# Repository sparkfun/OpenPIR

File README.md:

OpenPIR
==========

[![OpenPIR
Image](https://cdn.sparkfun.com/assets/parts/1/1/7/0/6/13968-01.jpg)*OpenPIR
(SEN-13968)*](https://www.sparkfun.com/products/13968)

OpenPIR is an open source general purpose passive long-wave infrared motion 
detection sensor.

Repository Contents
-------------------
* **/Documentation** - Datasheets for parts used in this design
* **/Hardware** - All Eagle design files
* **/Production** - Panel files used by SFE production for ordering

License Information
-------------------
The hardware is released under [Creative Commons Share-alike
4.0](http://creativecommons.org/licenses/by-sa/4.0/).  
All other code is open source so please feel free to do anything you want with
it; you buy me a beer if you use this and we meet someday ([Beerware
license](http://en.wikipedia.org/wiki/Beerware)).

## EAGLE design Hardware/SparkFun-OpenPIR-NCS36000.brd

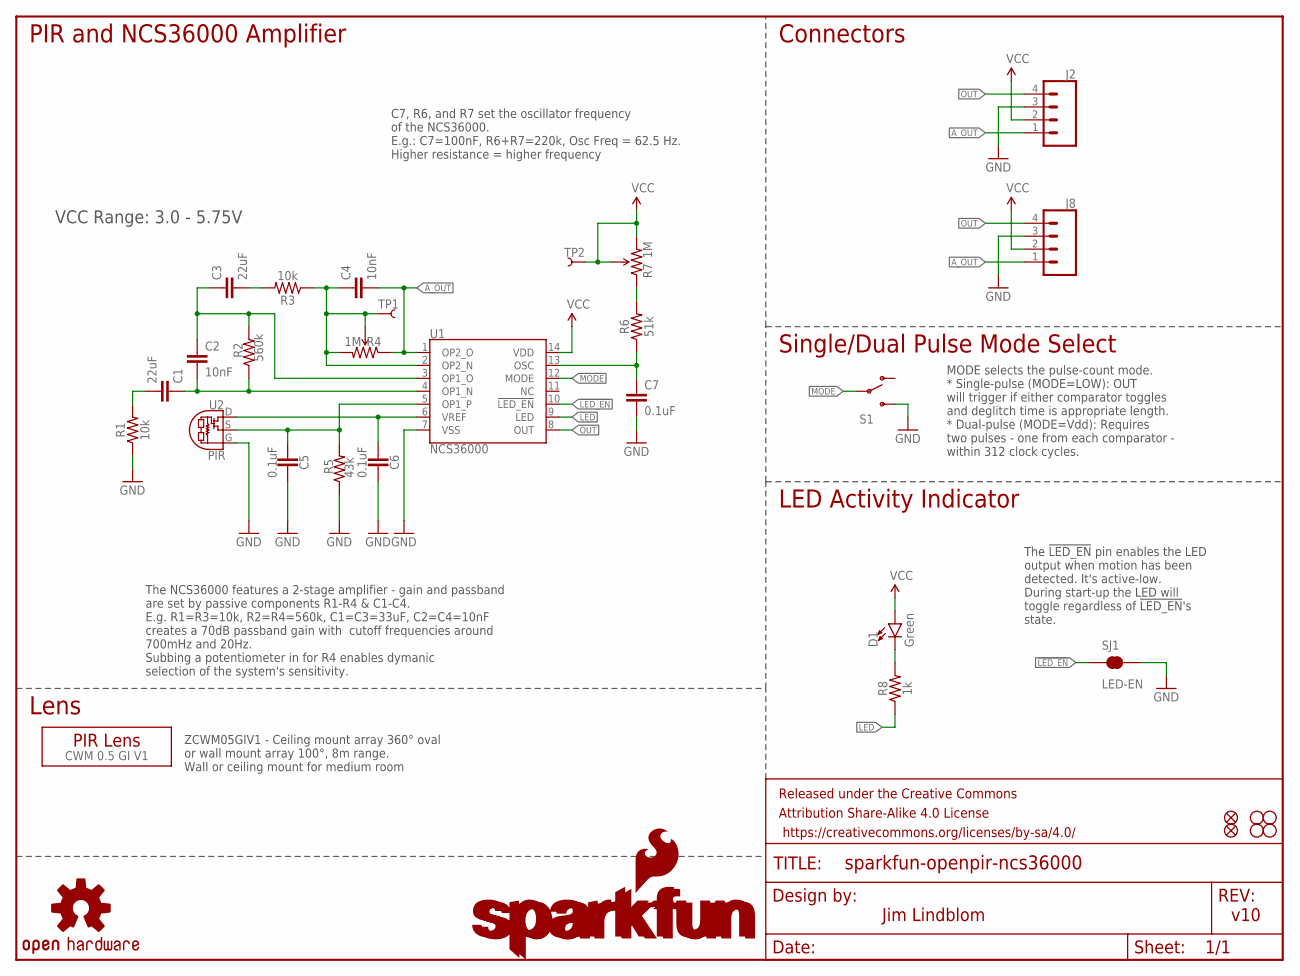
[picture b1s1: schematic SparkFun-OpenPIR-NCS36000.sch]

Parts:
C1, C3: 22uF; 0805
C2, C4: 10nF; 0603
C5, C6, C7: 0.1uF; 0603
D1: Green; LED-1206-BOTTOM
FD1, FD2: FIDUCIALUFIDUCIAL; MICRO-FIDUCIAL
FRAME1: FRAME-LETTER; CREATIVE_COMMONS
H1, H2, H3, H4: STAND-OFF
J2: CONN_04JST-PTH-VERT-NS; JST-4-PTH-VERT-NS
J8: CONN_04NO_SILK_ALL_ROUND; 1X04_NO_SILK_ALL_ROUND
LOGO1: SFE_LOGO_NAME_FLAME.1_INCH; SFE_LOGO_NAME_FLAME_.1
LOGO3: SFE_LOGO_NAME.1_INCH; SFE_LOGO_NAME_.1
LOGO4: OSHW-LOGOS; OSHW-LOGO-S
R1, R3: 10k; 0603
R2: 560k; 0603
R4, R7: 1M; TRIMPOT-TC33X
R5: 43k; 0603
R6: 51k; 0603
R8: 1k; 0603
S1: SWITCH-SPDT-SMD-A; SWITCH-SPST-SMD-A
SJ1: LED-EN; SJ_2S
TP1, TP2: TEST-POINT3X5; PAD.03X.05
U1: NCS36000; SO14
U2: PIR
U$1: CWM 0.5 GI V1; LENS-CWM-0.5-GI-V1

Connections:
!LED_EN!: SJ1.1, U1.10 (!LED_EN!)
A_OUT: C4.2, J2.1, J8.1, R4.1 (CCW), U1.1 (OP2_O)
GND: C5.2, C6.2, C7.2, J2.3, J8.3, R1.1, R5.1, S1.3 (S), SJ1.2, U1.7 (VSS), U2.G
LED: R8.1, U1.9 (LED)
MODE: S1.2, U1.12 (MODE)
unnamed: C5.1, R5.2, U1.5 (OP1_P), U2.S
unnamed: C6.1, U1.6 (VREF), U2.D
unnamed: C1.2, R1.2
unnamed: C3.2, R3.2
unnamed: C1.1, C2.2, R2.1, U1.4 (OP1_N)
unnamed: C2.1, C3.1, R2.2, U1.3 (OP1_O)
unnamed: C4.1, R3.1, R4.2 (WIPER), R4.3 (CW), TP1.P$1, U1.2 (OP2_N)
unnamed: C7.1, R6.1, U1.13 (OSC)
unnamed: D1.C, R8.2
unnamed: R6.2, R7.1 (CCW)
OUT: J2.4, J8.4, U1.8 (OUT)
VCC: D1.A, J2.2, J8.2, R7.2 (WIPER), R7.3 (CW), TP2.P$1, U1.14 (VDD)

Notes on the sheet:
The !LED_EN! pin enables the LED output when motion has been detected. It's active-low. During start-up the LED will toggle regardless of !LED_EN!'s state.
MODE selects the pulse-count mode. * Single-pulse (MODE=LOW): OUT will trigger if either comparator toggles and deglitch time is appropriate length. * Dual-pulse (MODE=Vdd): Requires two pulses - one from each comparator - within 312 clock cycles.
Jim Lindblom
v10
VCC Range: 3.0 - 5.75V
The NCS36000 features a 2-stage amplifier - gain and passband are set by passive components R1-R4 & C1-C4. E.g. R1=R3=10k, R2=R4=560k, C1=C3=33uF, C2=C4=10nF creates a 70dB passband gain with cutoff frequencies around 700mHz and 20Hz. Subbing a potentiometer in for R4 enables dymanic selection of t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
C7, R6, and R7 set the oscillator frequency of the NCS36000. E.g.: C7=100nF, R6+R7=220k, Osc Freq = 62.5 Hz. Higher resistance = higher frequency
ZCWM05GIV1 - Ceiling mount array 360° oval or wall mount array 100°, 8m range. Wall or ceiling mount for medium room
PIR and NCS36000 Amplifier
Connectors
Single/Dual Pulse Mode Select
LED Activity Indicator
Lens

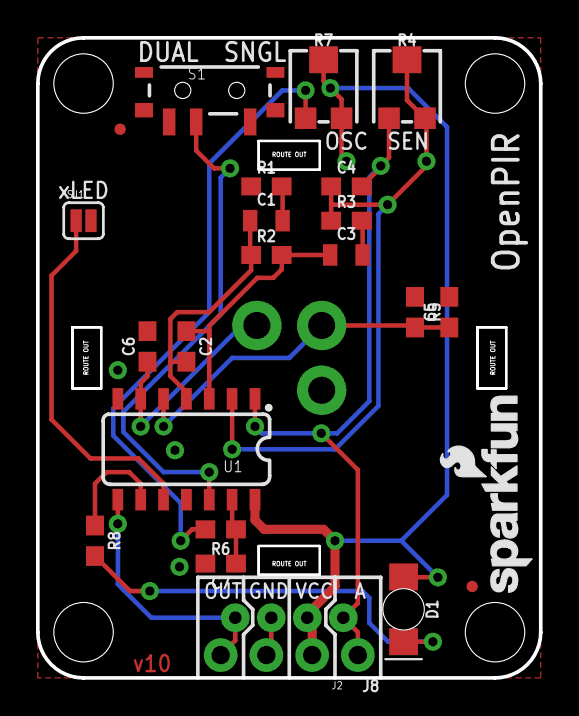
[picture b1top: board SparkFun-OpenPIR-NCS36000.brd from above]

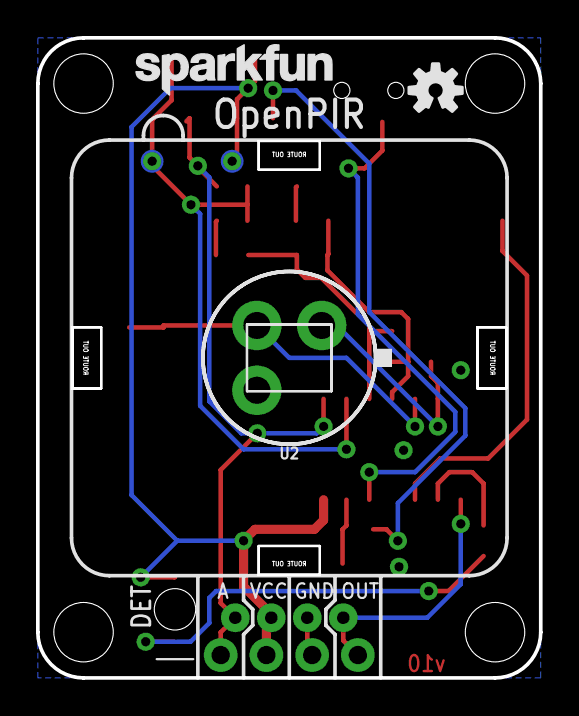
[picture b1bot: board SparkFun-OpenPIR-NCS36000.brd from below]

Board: 2 copper layers, 27.9 x 35.6 mm, 35 parts (6 on the bottom side), 17 nets.

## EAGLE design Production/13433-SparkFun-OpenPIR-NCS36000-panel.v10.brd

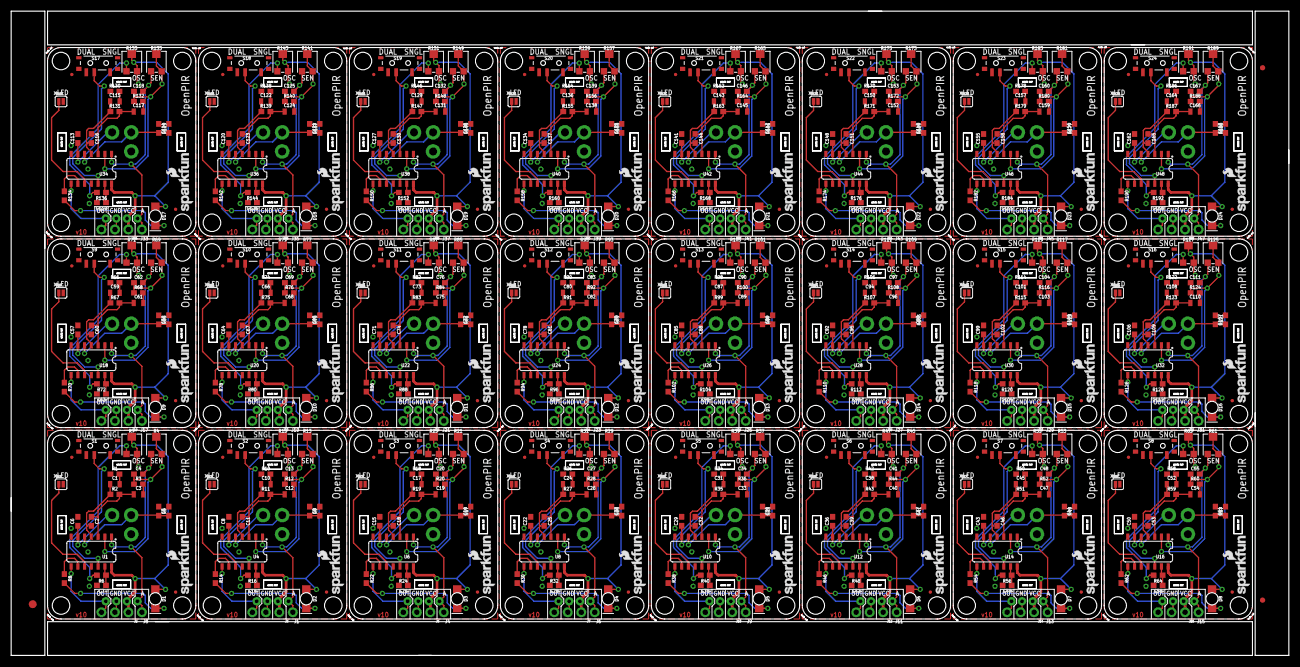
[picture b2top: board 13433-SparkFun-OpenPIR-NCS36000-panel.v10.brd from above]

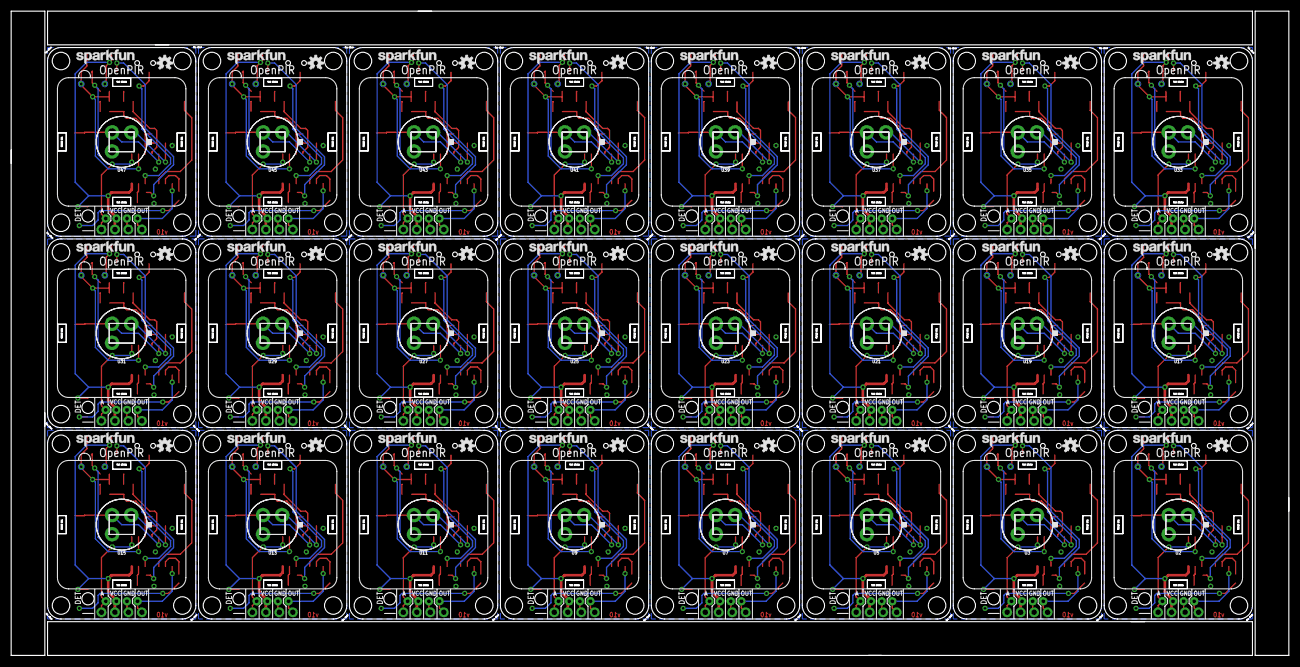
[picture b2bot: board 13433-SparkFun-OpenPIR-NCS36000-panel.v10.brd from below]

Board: 2 copper layers, 240.8 x 121.4 mm, 819 parts (144 on the bottom side), 408 nets.

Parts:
C1, C3, C10, C12, C17, C19, C24, C26, C31, C33, C38, C40, C45, C47, C52, C54, C59, C61, C66, C68, C73, C75, C80, C82, C87, C89, C94, C96, C101, C103, C108, C110, C115, C117, C122, C124, C129, C131, C136, C138, C143, C145, C150, C152, C157, C159, C164, C166: 22uF; 0805
C2, C4, C11, C13, C18, C20, C25, C27, C32, C34, C39, C41, C46, C48, C53, C55, C60, C62, C67, C69, C74, C76, C81, C83, C88, C90, C95, C97, C102, C104, C109, C111, C116, C118, C123, C125, C130, C132, C137, C139, C144, C146, C151, C153, C158, C160, C165, C167: 10nF; 0603
C5, C6, C7, C8, C9, C14, C15, C16, C21, C22, C23, C28, C29, C30, C35, C36, C37, C42, C43, C44, C49, C50, C51, C56, C57, C58, C63, C64, C65, C70, C71, C72, C77, C78, C79, C84, C85, C86, C91, C92, C93, C98, C99, C100, C105, C106, C107, C112, C113, C114, C119, C120, C121, C126, C127, C128, C133, C134, C135, C140, C141, C142, C147, C148, C149, C154, C155, C156, C161, C162, C163, C168: 0.1uF; 0603
D1, D2, D3, D4, D5, D6, D7, D8, D9, D10, D11, D12, D13, D14, D15, D16, D17, D18, D19, D20, D21, D22, D23, D24: Green; LED-1206-BOTTOM
E$1: FIDUCIAL-1.5X3
E$5, E$6: FIDUCIAL-1X2
FD1, FD2, FD3, FD4, FD5, FD6, FD7, FD8, FD9, FD10, FD11, FD12, FD13, FD14, FD15, FD16, FD17, FD18, FD19, FD20, FD21, FD22, FD23, FD24, FD25, FD26, FD27, FD28, FD29, FD30, FD31, FD32, FD33, FD34, FD35, FD36, FD37, FD38, FD39, FD40, FD41, FD42, FD43, FD44, FD45, FD46, FD47, FD48: FIDUCIALUFIDUCIAL; MICRO-FIDUCIAL
H1, H2, H3, H4, H5, H6, H7, H8, H9, H10, H11, H12, H13, H14, H15, H16, H17, H18, H19, H20, H21, H22, H23, H24, H25, H26, H27, H28, H29, H30, H31, H32, H33, H34, H35, H36, H37, H38, H39, H40, H41, H42, H43, H44, H45, H46, H47, H48, H49, H50, H51, H52, H53, H54, H55, H56, H57, H58, H59, H60, H61, H62, H63, H64, H65, H66, H67, H68, H69, H70, H71, H72, H73, H74, H75, H76, H77, H78, H79, H80, H81, H82, H83, H84, H85, H86, H87, H88, H89, H90, H91, H92, H93, H94, H95, H96: STAND-OFF
J1, J4, J6, J8, J9, J11, J13, J15, J17, J19, J21, J23, J25, J27, J29, J31, J33, J35, J37, J39, J41, J43, J45, J47: 1X04_NO_SILK_ALL_ROUND
J2, J3, J5, J7, J10, J12, J14, J16, J18, J20, J22, J24, J26, J28, J30, J32, J34, J36, J38, J40, J42, J44, J46, J48: JST-4-PTH-VERT-NS
LOGO1, LOGO2, LOGO7, LOGO10, LOGO13, LOGO16, LOGO19, LOGO22, LOGO25, LOGO28, LOGO31, LOGO34, LOGO37, LOGO40, LOGO43, LOGO46, LOGO49, LOGO52, LOGO55, LOGO58, LOGO61, LOGO64, LOGO67, LOGO70: SFE_LOGO_NAME_FLAME.1_INCH; SFE_LOGO_NAME_FLAME_.1
LOGO3, LOGO5, LOGO8, LOGO11, LOGO14, LOGO17, LOGO20, LOGO23, LOGO26, LOGO29, LOGO32, LOGO35, LOGO38, LOGO41, LOGO44, LOGO47, LOGO50, LOGO53, LOGO56, LOGO59, LOGO62, LOGO65, LOGO68, LOGO71: SFE_LOGO_NAME.1_INCH; SFE_LOGO_NAME_.1
LOGO4, LOGO6, LOGO9, LOGO12, LOGO15, LOGO18, LOGO21, LOGO24, LOGO27, LOGO30, LOGO33, LOGO36, LOGO39, LOGO42, LOGO45, LOGO48, LOGO51, LOGO54, LOGO57, LOGO60, LOGO63, LOGO66, LOGO69, LOGO72: OSHW-LOGOS; OSHW-LOGO-S
R1, R3, R10, R12, R18, R20, R26, R28, R34, R36, R42, R44, R50, R52, R58, R60, R66, R68, R74, R76, R82, R84, R90, R92, R98, R100, R106, R108, R114, R116, R122, R124, R130, R132, R138, R140, R146, R148, R154, R156, R162, R164, R170, R172, R178, R180, R186, R188: 10k; 0603
R2, R11, R19, R27, R35, R43, R51, R59, R67, R75, R83, R91, R99, R107, R115, R123, R131, R139, R147, R155, R163, R171, R179, R187: 560k; 0603
R4, R7, R13, R15, R21, R23, R29, R31, R37, R39, R45, R47, R53, R55, R61, R63, R69, R71, R77, R79, R85, R87, R93, R95, R101, R103, R109, R111, R117, R119, R125, R127, R133, R135, R141, R143, R149, R151, R157, R159, R165, R167, R173, R175, R181, R183, R189, R191: 1M; TRIMPOT-TC33X
R5, R9, R17, R25, R33, R41, R49, R57, R65, R73, R81, R89, R97, R105, R113, R121, R129, R137, R145, R153, R161, R169, R177, R185: 43k; 0603
R6, R16, R24, R32, R40, R48, R56, R64, R72, R80, R88, R96, R104, R112, R120, R128, R136, R144, R152, R160, R168, R176, R184, R192: 51k; 0603
R8, R14, R22, R30, R38, R46, R54, R62, R70, R78, R86, R94, R102, R110, R118, R126, R134, R142, R150, R158, R166, R174, R182, R190: 1k; 0603
S1, S2, S3, S4, S5, S6, S7, S8, S9, S10, S11, S12, S13, S14, S15, S16, S17, S18, S19, S20, S21, S22, S23, S24: SWITCH-SPST-SMD-A
SJ1, SJ2, SJ3, SJ4, SJ5, SJ6, SJ7, SJ8, SJ9, SJ10, SJ11, SJ12, SJ13, SJ14, SJ15, SJ16, SJ17, SJ18, SJ19, SJ20, SJ21, SJ22, SJ23, SJ24: LED-EN; SJ_2S
TP1, TP2, TP3, TP4, TP5, TP6, TP7, TP8, TP9, TP10, TP11, TP12, TP13, TP14, TP15, TP16, TP17, TP18, TP19, TP20, TP21, TP22, TP23, TP24, TP25, TP26, TP27, TP28, TP29, TP30, TP31, TP32, TP33, TP34, TP35, TP36, TP37, TP38, TP39, TP40, TP41, TP42, TP43, TP44, TP45, TP46, TP47, TP48: PAD.03X.05
U1, U4, U6, U8, U10, U12, U14, U16, U18, U20, U22, U24, U26, U28, U30, U32, U34, U36, U38, U40, U42, U44, U46, U48: NCS36000; SO14
U2, U3, U5, U7, U9, U11, U13, U15, U17, U19, U21, U23, U25, U27, U29, U31, U33, U35, U37, U39, U41, U43, U45, U47: PIR
U$1, U$2, U$3, U$4, U$5, U$6, U$7, U$8, U$9, U$10, U$11, U$12, U$13, U$14, U$15, U$16, U$17, U$18, U$19, U$20, U$21, U$22, U$23, U$24: CWM 0.5 GI V1; LENS-CWM-0.5-GI-V1

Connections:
!LED_EN!: SJ1.1, U1.10
!LED_EN!1: SJ2.1, U4.10
!LED_EN!2: SJ3.1, U6.10
!LED_EN!3: SJ4.1, U8.10
!LED_EN!4: SJ5.1, U10.10
!LED_EN!5: SJ6.1, U12.10
!LED_EN!6: SJ7.1, U14.10
!LED_EN!7: SJ8.1, U16.10
!LED_EN!8: SJ9.1, U18.10
!LED_EN!9: SJ10.1, U20.10
!LED_EN!10: SJ11.1, U22.10
!LED_EN!11: SJ12.1, U24.10
!LED_EN!12: SJ13.1, U26.10
!LED_EN!13: SJ14.1, U28.10
!LED_EN!14: SJ15.1, U30.10
!LED_EN!15: SJ16.1, U32.10
!LED_EN!16: SJ17.1, U34.10
!LED_EN!17: SJ18.1, U36.10
!LED_EN!18: SJ19.1, U38.10
!LED_EN!19: SJ20.1, U40.10
!LED_EN!20: SJ21.1, U42.10
!LED_EN!21: SJ22.1, U44.10
!LED_EN!22: SJ23.1, U46.10
!LED_EN!23: SJ24.1, U48.10
A_OUT: C4.2, J2.1, J8.1, R4.1, U1.1
A_OUT1: C13.2, J1.1, J3.1, R13.1, U4.1
A_OUT2: C20.2, J4.1, J5.1, R21.1, U6.1
A_OUT3: C27.2, J6.1, J7.1, R29.1, U8.1
A_OUT4: C34.2, J9.1, J10.1, R37.1, U10.1
A_OUT5: C41.2, J11.1, J12.1, R45.1, U12.1
A_OUT6: C48.2, J13.1, J14.1, R53.1, U14.1
A_OUT7: C55.2, J15.1, J16.1, R61.1, U16.1
A_OUT8: C62.2, J17.1, J18.1, R69.1, U18.1
A_OUT9: C69.2, J19.1, J20.1, R77.1, U20.1
A_OUT10: C76.2, J21.1, J22.1, R85.1, U22.1
A_OUT11: C83.2, J23.1, J24.1, R93.1, U24.1
A_OUT12: C90.2, J25.1, J26.1, R101.1, U26.1
A_OUT13: C97.2, J27.1, J28.1, R109.1, U28.1
A_OUT14: C104.2, J29.1, J30.1, R117.1, U30.1
A_OUT15: C111.2, J31.1, J32.1, R125.1, U32.1
A_OUT16: C118.2, J33.1, J34.1, R133.1, U34.1
A_OUT17: C125.2, J35.1, J36.1, R141.1, U36.1
A_OUT18: C132.2, J37.1, J38.1, R149.1, U38.1
A_OUT19: C139.2, J39.1, J40.1, R157.1, U40.1
A_OUT20: C146.2, J41.1, J42.1, R165.1, U42.1
A_OUT21: C153.2, J43.1, J44.1, R173.1, U44.1
A_OUT22: C160.2, J45.1, J46.1, R181.1, U46.1
A_OUT23: C167.2, J47.1, J48.1, R189.1, U48.1
GND: C5.2, C6.2, C7.2, J2.3, J8.3, R1.1, R5.1, S1.3, SJ1.2, U1.7, U2.G
GND1: C8.2, C9.2, C14.2, J1.3, J3.3, R9.1, R10.1, S2.3, SJ2.2, U3.G, U4.7
GND2: C15.2, C16.2, C21.2, J4.3, J5.3, R17.1, R18.1, S3.3, SJ3.2, U5.G, U6.7
GND3: C22.2, C23.2, C28.2, J6.3, J7.3, R25.1, R26.1, S4.3, SJ4.2, U7.G, U8.7
GND4: C29.2, C30.2, C35.2, J9.3, J10.3, R33.1, R34.1, S5.3, SJ5.2, U9.G, U10.7
GND5: C36.2, C37.2, C42.2, J11.3, J12.3, R41.1, R42.1, S6.3, SJ6.2, U11.G, U12.7
GND6: C43.2, C44.2, C49.2, J13.3, J14.3, R49.1, R50.1, S7.3, SJ7.2, U13.G, U14.7
GND7: C50.2, C51.2, C56.2, J15.3, J16.3, R57.1, R58.1, S8.3, SJ8.2, U15.G, U16.7
GND8: C57.2, C58.2, C63.2, J17.3, J18.3, R65.1, R66.1, S9.3, SJ9.2, U17.G, U18.7
GND9: C64.2, C65.2, C70.2, J19.3, J20.3, R73.1, R74.1, S10.3, SJ10.2, U19.G, U20.7
GND10: C71.2, C72.2, C77.2, J21.3, J22.3, R81.1, R82.1, S11.3, SJ11.2, U21.G, U22.7
GND11: C78.2, C79.2, C84.2, J23.3, J24.3, R89.1, R90.1, S12.3, SJ12.2, U23.G, U24.7
GND12: C85.2, C86.2, C91.2, J25.3, J26.3, R97.1, R98.1, S13.3, SJ13.2, U25.G, U26.7
GND13: C92.2, C93.2, C98.2, J27.3, J28.3, R105.1, R106.1, S14.3, SJ14.2, U27.G, U28.7
GND14: C99.2, C100.2, C105.2, J29.3, J30.3, R113.1, R114.1, S15.3, SJ15.2, U29.G, U30.7
GND15: C106.2, C107.2, C112.2, J31.3, J32.3, R121.1, R122.1, S16.3, SJ16.2, U31.G, U32.7
GND16: C113.2, C114.2, C119.2, J33.3, J34.3, R129.1, R130.1, S17.3, SJ17.2, U33.G, U34.7
GND17: C120.2, C121.2, C126.2, J35.3, J36.3, R137.1, R138.1, S18.3, SJ18.2, U35.G, U36.7
GND18: C127.2, C128.2, C133.2, J37.3, J38.3, R145.1, R146.1, S19.3, SJ19.2, U37.G, U38.7
GND19: C134.2, C135.2, C140.2, J39.3, J40.3, R153.1, R154.1, S20.3, SJ20.2, U39.G, U40.7
GND20: C141.2, C142.2, C147.2, J41.3, J42.3, R161.1, R162.1, S21.3, SJ21.2, U41.G, U42.7
GND21: C148.2, C149.2, C154.2, J43.3, J44.3, R169.1, R170.1, S22.3, SJ22.2, U43.G, U44.7
GND22: C155.2, C156.2, C161.2, J45.3, J46.3, R177.1, R178.1, S23.3, SJ23.2, U45.G, U46.7
GND23: C162.2, C163.2, C168.2, J47.3, J48.3, R185.1, R186.1, S24.3, SJ24.2, U47.G, U48.7
LED: R8.1, U1.9
LED1: R14.1, U4.9
LED2: R22.1, U6.9
LED3: R30.1, U8.9
LED4: R38.1, U10.9
LED5: R46.1, U12.9
LED6: R54.1, U14.9
LED7: R62.1, U16.9
LED8: R70.1, U18.9
LED9: R78.1, U20.9
LED10: R86.1, U22.9
LED11: R94.1, U24.9
LED12: R102.1, U26.9
LED13: R110.1, U28.9
LED14: R118.1, U30.9
LED15: R126.1, U32.9
LED16: R134.1, U34.9
LED17: R142.1, U36.9
LED18: R150.1, U38.9
LED19: R158.1, U40.9
LED20: R166.1, U42.9
LED21: R174.1, U44.9
LED22: R182.1, U46.9
LED23: R190.1, U48.9
MODE: S1.2, U1.12
MODE1: S2.2, U4.12
MODE2: S3.2, U6.12
MODE3: S4.2, U8.12
MODE4: S5.2, U10.12
MODE5: S6.2, U12.12
MODE6: S7.2, U14.12
MODE7: S8.2, U16.12
MODE8: S9.2, U18.12
MODE9: S10.2, U20.12
MODE10: S11.2, U22.12
MODE11: S12.2, U24.12
MODE12: S13.2, U26.12
MODE13: S14.2, U28.12
MODE14: S15.2, U30.12
MODE15: S16.2, U32.12
MODE16: S17.2, U34.12
MODE17: S18.2, U36.12
MODE18: S19.2, U38.12
MODE19: S20.2, U40.12
MODE20: S21.2, U42.12
MODE21: S22.2, U44.12
MODE22: S23.2, U46.12
MODE23: S24.2, U48.12
unnamed: C5.1, R5.2, U1.5, U2.S
unnamed: C6.1, U1.6, U2.D
unnamed: C1.2, R1.2
unnamed: C3.2, R3.2
unnamed: C1.1, C2.2, R2.1, U1.4
unnamed: C2.1, C3.1, R2.2, U1.3
unnamed: C4.1, R3.1, R4.2, R4.3, TP1.P$1, U1.2
unnamed: C7.1, R6.1, U1.13
unnamed: D1.C, R8.2
unnamed: C8.1, U3.D, U4.6
unnamed: R6.2, R7.1
unnamed: C9.1, R9.2, U3.S, U4.5
unnamed: C10.2, R10.2
unnamed: C12.2, R12.2
unnamed: C10.1, C11.2, R11.1, U4.4
unnamed: C11.1, C12.1, R11.2, U4.3
unnamed: C13.1, R12.1, R13.2, R13.3, TP3.P$1, U4.2
unnamed: C14.1, R16.1, U4.13
unnamed: D2.C, R14.2
unnamed: R15.1, R16.2
unnamed: C15.1, U5.D, U6.6
unnamed: C16.1, R17.2, U5.S, U6.5
unnamed: C17.2, R18.2
unnamed: C19.2, R20.2
unnamed: C17.1, C18.2, R19.1, U6.4
unnamed: C18.1, C19.1, R19.2, U6.3
unnamed: C20.1, R20.1, R21.2, R21.3, TP5.P$1, U6.2
unnamed: C21.1, R24.1, U6.13
unnamed: D3.C, R22.2
unnamed: R23.1, R24.2
unnamed: C22.1, U7.D, U8.6
unnamed: C23.1, R25.2, U7.S, U8.5
unnamed: C24.2, R26.2
unnamed: C26.2, R28.2
unnamed: C24.1, C25.2, R27.1, U8.4
unnamed: C25.1, C26.1, R27.2, U8.3
unnamed: C27.1, R28.1, R29.2, R29.3, TP7.P$1, U8.2
unnamed: C28.1, R32.1, U8.13
unnamed: D4.C, R30.2
unnamed: R31.1, R32.2
unnamed: C29.1, U9.D, U10.6
unnamed: C30.1, R33.2, U9.S, U10.5
unnamed: C31.2, R34.2
unnamed: C33.2, R36.2
unnamed: C31.1, C32.2, R35.1, U10.4
unnamed: C32.1, C33.1, R35.2, U10.3
unnamed: C34.1, R36.1, R37.2, R37.3, TP9.P$1, U10.2
unnamed: C35.1, R40.1, U10.13
unnamed: D5.C, R38.2
unnamed: R39.1, R40.2
unnamed: C36.1, U11.D, U12.6
unnamed: C37.1, R41.2, U11.S, U12.5
unnamed: C38.2, R42.2
unnamed: C40.2, R44.2
unnamed: C38.1, C39.2, R43.1, U12.4
unnamed: C39.1, C40.1, R43.2, U12.3
unnamed: C41.1, R44.1, R45.2, R45.3, TP11.P$1, U12.2
unnamed: C42.1, R48.1, U12.13
unnamed: D6.C, R46.2
unnamed: R47.1, R48.2
unnamed: C43.1, U13.D, U14.6
unnamed: C44.1, R49.2, U13.S, U14.5
unnamed: C45.2, R50.2
unnamed: C47.2, R52.2
unnamed: C45.1, C46.2, R51.1, U14.4
unnamed: C46.1, C47.1, R51.2, U14.3
unnamed: C48.1, R52.1, R53.2, R53.3, TP13.P$1, U14.2
unnamed: C49.1, R56.1, U14.13
unnamed: D7.C, R54.2
unnamed: R55.1, R56.2
unnamed: C50.1, U15.D, U16.6
unnamed: C51.1, R57.2, U15.S, U16.5
unnamed: C52.2, R58.2
unnamed: C54.2, R60.2
unnamed: C52.1, C53.2, R59.1, U16.4
unnamed: C53.1, C54.1, R59.2, U16.3
unnamed: C55.1, R60.1, R61.2, R61.3, TP15.P$1, U16.2
unnamed: C56.1, R64.1, U16.13
unnamed: D8.C, R62.2
unnamed: R63.1, R64.2
unnamed: C57.1, U17.D, U18.6
unnamed: C58.1, R65.2, U17.S, U18.5
unnamed: C59.2, R66.2
unnamed: C61.2, R68.2
unnamed: C59.1, C60.2, R67.1, U18.4
unnamed: C60.1, C61.1, R67.2, U18.3
unnamed: C62.1, R68.1, R69.2, R69.3, TP17.P$1, U18.2
unnamed: C63.1, R72.1, U18.13
unnamed: D9.C, R70.2
unnamed: R71.1, R72.2
unnamed: C64.1, U19.D, U20.6
unnamed: C65.1, R73.2, U19.S, U20.5
unnamed: C66.2, R74.2
unnamed: C68.2, R76.2
unnamed: C66.1, C67.2, R75.1, U20.4
unnamed: C67.1, C68.1, R75.2, U20.3
unnamed: C69.1, R76.1, R77.2, R77.3, TP19.P$1, U20.2
unnamed: C70.1, R80.1, U20.13
unnamed: D10.C, R78.2
unnamed: R79.1, R80.2
unnamed: C71.1, U21.D, U22.6
unnamed: C72.1, R81.2, U21.S, U22.5
unnamed: C73.2, R82.2
unnamed: C75.2, R84.2
unnamed: C73.1, C74.2, R83.1, U22.4
unnamed: C74.1, C75.1, R83.2, U22.3
unnamed: C76.1, R84.1, R85.2, R85.3, TP21.P$1, U22.2
unnamed: C77.1, R88.1, U22.13
unnamed: D11.C, R86.2
unnamed: R87.1, R88.2
unnamed: C78.1, U23.D, U24.6
unnamed: C79.1, R89.2, U23.S, U24.5
unnamed: C80.2, R90.2
unnamed: C82.2, R92.2
unnamed: C80.1, C81.2, R91.1, U24.4
unnamed: C81.1, C82.1, R91.2, U24.3
unnamed: C83.1, R92.1, R93.2, R93.3, TP23.P$1, U24.2
unnamed: C84.1, R96.1, U24.13
unnamed: D12.C, R94.2
unnamed: R95.1, R96.2
unnamed: C85.1, U25.D, U26.6
unnamed: C86.1, R97.2, U25.S, U26.5
unnamed: C87.2, R98.2
unnamed: C89.2, R100.2
unnamed: C87.1, C88.2, R99.1, U26.4
unnamed: C88.1, C89.1, R99.2, U26.3
unnamed: C90.1, R100.1, R101.2, R101.3, TP25.P$1, U26.2
unnamed: C91.1, R104.1, U26.13
unnamed: D13.C, R102.2
unnamed: R103.1, R104.2
unnamed: C92.1, U27.D, U28.6
unnamed: C93.1, R105.2, U27.S, U28.5
unnamed: C94.2, R106.2
unnamed: C96.2, R108.2
unnamed: C94.1, C95.2, R107.1, U28.4
unnamed: C95.1, C96.1, R107.2, U28.3
unnamed: C97.1, R108.1, R109.2, R109.3, TP27.P$1, U28.2
unnamed: C98.1, R112.1, U28.13
unnamed: D14.C, R110.2
unnamed: R111.1, R112.2
unnamed: C99.1, U29.D, U30.6
unnamed: C100.1, R113.2, U29.S, U30.5
unnamed: C101.2, R114.2
unnamed: C103.2, R116.2
unnamed: C101.1, C102.2, R115.1, U30.4
unnamed: C102.1, C103.1, R115.2, U30.3
unnamed: C104.1, R116.1, R117.2, R117.3, TP29.P$1, U30.2
unnamed: C105.1, R120.1, U30.13
unnamed: D15.C, R118.2
unnamed: R119.1, R120.2
unnamed: C106.1, U31.D, U32.6
unnamed: C107.1, R121.2, U31.S, U32.5
unnamed: C108.2, R122.2
unnamed: C110.2, R124.2
unnamed: C108.1, C109.2, R123.1, U32.4
unnamed: C109.1, C110.1, R123.2, U32.3
unnamed: C111.1, R124.1, R125.2, R125.3, TP31.P$1, U32.2
unnamed: C112.1, R128.1, U32.13
unnamed: D16.C, R126.2
unnamed: R127.1, R128.2
unnamed: C113.1, U33.D, U34.6
unnamed: C114.1, R129.2, U33.S, U34.5
unnamed: C115.2, R130.2
unnamed: C117.2, R132.2
unnamed: C115.1, C116.2, R131.1, U34.4
unnamed: C116.1, C117.1, R131.2, U34.3
unnamed: C118.1, R132.1, R133.2, R133.3, TP33.P$1, U34.2
unnamed: C119.1, R136.1, U34.13
unnamed: D17.C, R134.2
unnamed: R135.1, R136.2
unnamed: C120.1, U35.D, U36.6
unnamed: C121.1, R137.2, U35.S, U36.5
unnamed: C122.2, R138.2
unnamed: C124.2, R140.2
unnamed: C122.1, C123.2, R139.1, U36.4
unnamed: C123.1, C124.1, R139.2, U36.3
unnamed: C125.1, R140.1, R141.2, R141.3, TP35.P$1, U36.2
unnamed: C126.1, R144.1, U36.13
unnamed: D18.C, R142.2
unnamed: R143.1, R144.2
unnamed: C127.1, U37.D, U38.6
unnamed: C128.1, R145.2, U37.S, U38.5
unnamed: C129.2, R146.2
unnamed: C131.2, R148.2
unnamed: C129.1, C130.2, R147.1, U38.4
unnamed: C130.1, C131.1, R147.2, U38.3
unnamed: C132.1, R148.1, R149.2, R149.3, TP37.P$1, U38.2
unnamed: C133.1, R152.1, U38.13
unnamed: D19.C, R150.2
unnamed: R151.1, R152.2
unnamed: C134.1, U39.D, U40.6
unnamed: C135.1, R153.2, U39.S, U40.5
unnamed: C136.2, R154.2
unnamed: C138.2, R156.2
unnamed: C136.1, C137.2, R155.1, U40.4
unnamed: C137.1, C138.1, R155.2, U40.3
unnamed: C139.1, R156.1, R157.2, R157.3, TP39.P$1, U40.2
unnamed: C140.1, R160.1, U40.13
unnamed: D20.C, R158.2
unnamed: R159.1, R160.2
unnamed: C141.1, U41.D, U42.6
unnamed: C142.1, R161.2, U41.S, U42.5
unnamed: C143.2, R162.2
unnamed: C145.2, R164.2
unnamed: C143.1, C144.2, R163.1, U42.4
unnamed: C144.1, C145.1, R163.2, U42.3
unnamed: C146.1, R164.1, R165.2, R165.3, TP41.P$1, U42.2
unnamed: C147.1, R168.1, U42.13
unnamed: D21.C, R166.2
unnamed: R167.1, R168.2
unnamed: C148.1, U43.D, U44.6
unnamed: C149.1, R169.2, U43.S, U44.5
unnamed: C150.2, R170.2
unnamed: C152.2, R172.2
unnamed: C150.1, C151.2, R171.1, U44.4
unnamed: C151.1, C152.1, R171.2, U44.3
unnamed: C153.1, R172.1, R173.2, R173.3, TP43.P$1, U44.2
unnamed: C154.1, R176.1, U44.13
unnamed: D22.C, R174.2
unnamed: R175.1, R176.2
unnamed: C155.1, U45.D, U46.6
unnamed: C156.1, R177.2, U45.S, U46.5
unnamed: C157.2, R178.2
unnamed: C159.2, R180.2
unnamed: C157.1, C158.2, R179.1, U46.4
unnamed: C158.1, C159.1, R179.2, U46.3
unnamed: C160.1, R180.1, R181.2, R181.3, TP45.P$1, U46.2
unnamed: C161.1, R184.1, U46.13
unnamed: D23.C, R182.2
unnamed: R183.1, R184.2
unnamed: C162.1, U47.D, U48.6
unnamed: C163.1, R185.2, U47.S, U48.5
unnamed: C164.2, R186.2
unnamed: C166.2, R188.2
unnamed: C164.1, C165.2, R187.1, U48.4
unnamed: C165.1, C166.1, R187.2, U48.3
unnamed: C167.1, R188.1, R189.2, R189.3, TP47.P$1, U48.2
unnamed: C168.1, R192.1, U48.13
unnamed: D24.C, R190.2
unnamed: R191.1, R192.2
OUT: J2.4, J8.4, U1.8
OUT1: J1.4, J3.4, U4.8
OUT2: J4.4, J5.4, U6.8
OUT3: J6.4, J7.4, U8.8
OUT4: J9.4, J10.4, U10.8
OUT5: J11.4, J12.4, U12.8
OUT6: J13.4, J14.4, U14.8
OUT7: J15.4, J16.4, U16.8
OUT8: J17.4, J18.4, U18.8
OUT9: J19.4, J20.4, U20.8
OUT10: J21.4, J22.4, U22.8
OUT11: J23.4, J24.4, U24.8
OUT12: J25.4, J26.4, U26.8
OUT13: J27.4, J28.4, U28.8
OUT14: J29.4, J30.4, U30.8
OUT15: J31.4, J32.4, U32.8
OUT16: J33.4, J34.4, U34.8
OUT17: J35.4, J36.4, U36.8
OUT18: J37.4, J38.4, U38.8
OUT19: J39.4, J40.4, U40.8
OUT20: J41.4, J42.4, U42.8
OUT21: J43.4, J44.4, U44.8
OUT22: J45.4, J46.4, U46.8
OUT23: J47.4, J48.4, U48.8
VCC: D1.A, J2.2, J8.2, R7.2, R7.3, TP2.P$1, U1.14
VCC1: D2.A, J1.2, J3.2, R15.2, R15.3, TP4.P$1, U4.14
VCC2: D3.A, J4.2, J5.2, R23.2, R23.3, TP6.P$1, U6.14
VCC3: D4.A, J6.2, J7.2, R31.2, R31.3, TP8.P$1, U8.14
VCC4: D5.A, J9.2, J10.2, R39.2, R39.3, TP10.P$1, U10.14
VCC5: D6.A, J11.2, J12.2, R47.2, R47.3, TP12.P$1, U12.14
VCC6: D7.A, J13.2, J14.2, R55.2, R55.3, TP14.P$1, U14.14
VCC7: D8.A, J15.2, J16.2, R63.2, R63.3, TP16.P$1, U16.14
VCC8: D9.A, J17.2, J18.2, R71.2, R71.3, TP18.P$1, U18.14
VCC9: D10.A, J19.2, J20.2, R79.2, R79.3, TP20.P$1, U20.14
VCC10: D11.A, J21.2, J22.2, R87.2, R87.3, TP22.P$1, U22.14
VCC11: D12.A, J23.2, J24.2, R95.2, R95.3, TP24.P$1, U24.14
VCC12: D13.A, J25.2, J26.2, R103.2, R103.3, TP26.P$1, U26.14
VCC13: D14.A, J27.2, J28.2, R111.2, R111.3, TP28.P$1, U28.14
VCC14: D15.A, J29.2, J30.2, R119.2, R119.3, TP30.P$1, U30.14
VCC15: D16.A, J31.2, J32.2, R127.2, R127.3, TP32.P$1, U32.14
VCC16: D17.A, J33.2, J34.2, R135.2, R135.3, TP34.P$1, U34.14
VCC17: D18.A, J35.2, J36.2, R143.2, R143.3, TP36.P$1, U36.14
VCC18: D19.A, J37.2, J38.2, R151.2, R151.3, TP38.P$1, U38.14
VCC19: D20.A, J39.2, J40.2, R159.2, R159.3, TP40.P$1, U40.14
VCC20: D21.A, J41.2, J42.2, R167.2, R167.3, TP42.P$1, U42.14
VCC21: D22.A, J43.2, J44.2, R175.2, R175.3, TP44.P$1, U44.14
VCC22: D23.A, J45.2, J46.2, R183.2, R183.3, TP46.P$1, U46.14
VCC23: D24.A, J47.2, J48.2, R191.2, R191.3, TP48.P$1, U48.14

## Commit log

2016-06-20 Initial commit of hardware.
2016-06-21 Swapping 33uF cap packages to 1206.
2016-06-21 Updating sch and brd after running checklist.
2016-06-24 Moving route out text to design.
2016-06-24 created PROTO panel v01
2017-01-04 Fixing ZNCL11 tab route-out placement.
2017-01-04 Remove a few lenses, re-wire pot, re-routing
    - Removed ZAA09GIT1 lens & PTH holes that would hold it in. (Would be mounted at incorrect curve/distance.)
    - Removed ZNCL11 lens. Low stock, uncommon footprint.
    - Re-wired sensitivity pot so "turning it up" increases sensitivity.
    - Re-routing now that there are fewer mill-outs and holes.
2017-01-04 Moving xLED jumper to more accessible location
2017-01-09 Removing tStop from PIR sensor - expose copper on solder-side only.
2017-01-09 Revising pin labels
2017-01-10 Adding test points to trimpot wipers
2017-01-10 Replacing text logo with text+flame, moving schematic fids.
2017-01-11 Adding dimension layer outline to lens notch cutouts.
2017-01-31 Minor silkscreen adjustments. Incrementing to v10.
2017-02-02 Fixing lens silkscreen, and moving r's, c's away from PIR sensor.
2017-02-07 Adding description to PIR lens.
2017-02-07 Moving C6 a bit, minor re-routing.
2017-02-10 panel
2017-05-01 Fix image link in README.md

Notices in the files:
parts and their libraries:
SparkFun-Aesthetics: Licensing: Creative Commons ShareAlike 4.0 International - https://creativecommons.org/licenses/by-sa/4.0
SparkFun-Aesthetics: Released under the Creative Commons Attribution Share-Alike 4.0 License
SparkFun-Aesthetics: https://creativecommons.org/licenses/by-sa/4.0
